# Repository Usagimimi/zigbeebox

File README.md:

# zigbeebox
Powerful zigbee coordinator with USB and debug port in metal enclosure.

### This project is still under development!!! 

## Description
[Zigbee in general.](https://en.wikipedia.org/wiki/Zigbee)

The coordinator is the central unit of the zigbee network, handling significant RF traffic in most cases. This project offers low-cost open-source hardware for this task, as a remix of many DIY coordinators out there. Takes a bit of time and basic soldering skills to assemble, but it can replace any manufacturers proprietary device when ready. Using the right firmware and server application, you can build a reliable, secure zigbee network without factory restrictions, involving almost any zigbee appliance. This opens the possibility to use IKEA Tradfri lights along with Xiaomi sensors, Philips Hue products, and many more in the same network, without the vendors gateway. The pcb utilizes a cheap chinese CC2538+CC2592 RF module with ARM Cortex-M3 based SoC and enough memory to serve a lot of connections with good performance.

The design heavily relies on open-source code, such as [Zigbee2MQTT](https://www.zigbee2mqtt.io) and various firmware.

## Features
* Zigbee 3.0 capable SoC with external antenna connector and RF amplifier frontend
* Use mostly THT and superior SMD components to allow soldering by hand with average tools
* PCB dimensions are designed to fit in a cheap metal enclosure for better shielding
* Avoid dongle-style layout to assist final placement away from any interference
* Mounted with convenient USB Type-C receptacle, detach & orientation sensing
* Plug & play firmware flashing on the J-Link compatible 20pin IDC header
* Indicator LEDs for power, allow join mode, ZNP activity (RF traffic)
* Self-regenerating polyfuse protection for USB host & device

*Since the pcb applies a considerable amount of copper under the CC2538+CC2592 module, it is highly recommended to use the IPEX connector and connect an external antenna, even without metal enclosure.*

## PCB BOM
The following components are needed to assemble the coordinator.

| Component  | Type | Package | Value | Quantity |
| ---------- | ---- | ------- | ----- | -------- |
| F1 | Polyfuse | SMD-1206 | Ih=250mA, It=500mA | 1 |
| R1-R2 | Resistor | SMD-1206 | 33Ω | 2 |
| R3 | Resistor | SMD-1206 | 1.5kΩ | 1 |
| R4-R6 | Resistor | SMD-1206 | 100Ω | 3 |
| R7 | Resistor | SMD-1206 | 1kΩ | 1 |
| R8-R9 | Resistor | SMD-1206 | 5.1kΩ | 2 |
| C1-C2 | Tantalum capacitor | SMD-1206 | 10uF | 2 |
| C3 | Capacitor | SMD-1206 | 100nF | 1 |
| C4-C5 | Capacitor | SMD-1206 | 47pF | 2 |
| PWR-JOIN-ACT | LED | 3mm THT | Vf=2.2V, If=10mA | 3 |
| LD1117 | Voltage regulator | SOT223 | LD1117S33TR | 1 |
| USB-C | Receptacle | 16-pin THT | GCT USB4085 | 1 |
| RESET | Tactile switch | 3-pin THT 4.5x4.5mm | TS-C017 | 1 |
| JLINK-JTAG | Connector | 2.54mm IDC double row | 20-pin keyed male | 1 |
| Pin header | Connector | 2.54mm single row | 4-pin male | 1 |

Additional parts:

| Component  | Type | Package | Quantity | Source |
| ---------- | ---- | ------- | -------- | ------ |
| *[CC2538+CC2592 Module](https://github.com/uzsito/CC2538-CC2592-kicad-component)* | *Zigbee RF board* | *33-pin 20.5x33mmm* | *1* | Aliexpress, Ebay |

## Flashing
You can download and burn compiled firmware from the following repositories:

| Repository  | Firmware | Tested |
| --------- | --------- | ------ |
| [reverieline/CC2538-CC2592-ZNP](https://github.com/reverieline/CC2538-CC2592-ZNP) | MODKAMRU_V3_USB.hex | Tested |
| [antst/CC2538-ZNP-Coordinator-firmware](https://github.com/antst/CC2538-ZNP-Coordinator-firmware) | | Not tested |
| [Koenkk/Z-Stack-firmware](https://github.com/Koenkk/Z-Stack-firmware) | | Not tested |

Flashing methods:
* Using [J-link and J-Flash application](https://github.com/uzsito/zigbeebox/wiki/Flashing-with-JLink), connecting to 20-pin header with ribbon cable (Tested)
* Using [Raspberry Pi and OpenOCD](https://gist.github.com/hwhw/fc43892785aa84913d03495c97b0f25a) connecting with dupont wires (Not tested)

## Enclosure
It is optional to [put the board in a cheap metal case](https://github.com/uzsito/zigbeebox/wiki/Installing-in-metal-box) to achieve better shielding and appearance. The finished pcb fits perfectly in a common box by design, with an applied pigtail to connect your external antenna.

*Finished photos and cutout templates coming soon.*

Former prototype:

## Assembly and application
1. Clone or download this repository.
2. Use the prebuilt [gerber archive](kicad_board/gerber/zigbeebox.zip) to print the pcb. Any chinese manufacturer (JLPCB, ALLPCB, PCBWAY, etc.) can fabricate a copy for a couple dollars. Really, it's dirt cheap.
3. Once you got the pcb and the listed components, assemble the coordinator by hand soldering, no special tool needed.
4. Flash the desired firmware with one of the available methods.
5. Connect the board to a machine running zigbee2mqtt or other zigbee server application, and check the log for your new coordinator.

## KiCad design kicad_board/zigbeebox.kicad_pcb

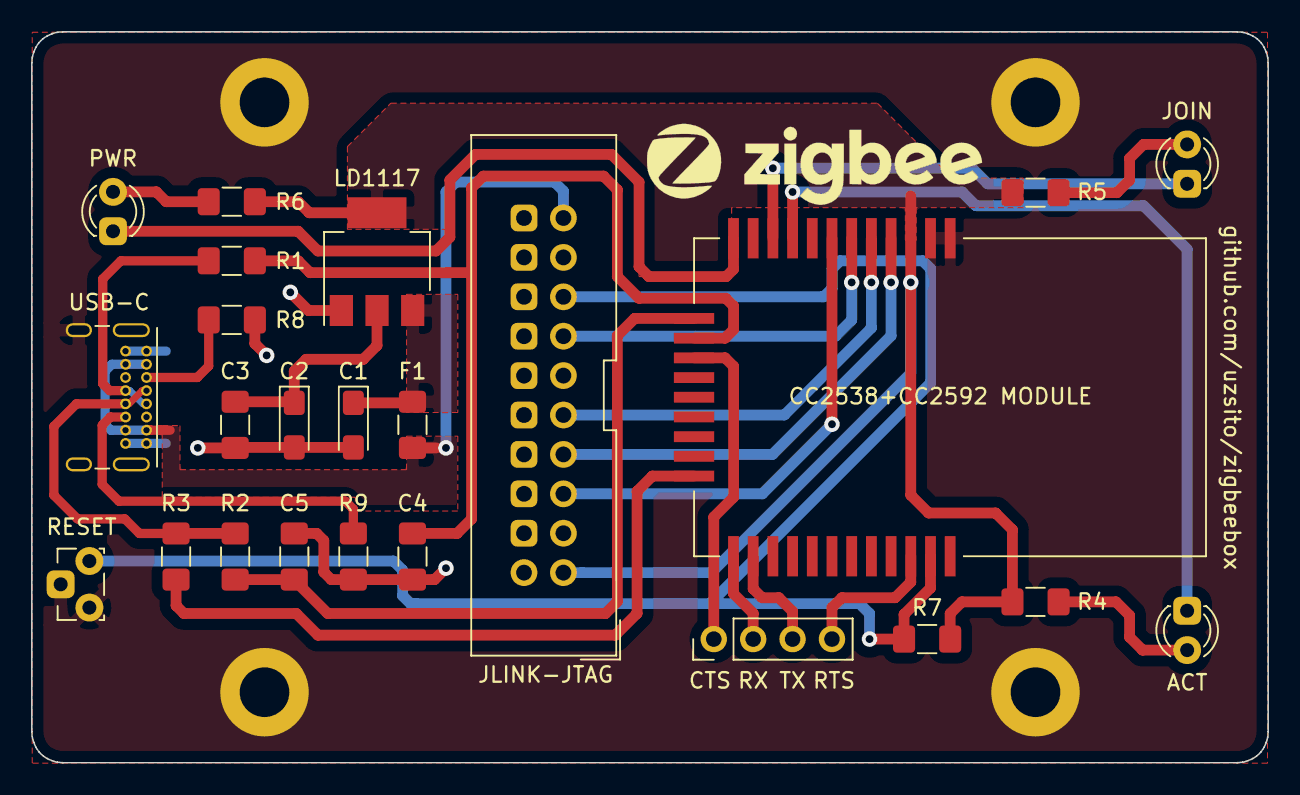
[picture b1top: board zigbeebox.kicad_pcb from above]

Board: 2 copper layers, 79.7 x 47.1 mm, 28 parts (0 on the bottom side), 26 nets.

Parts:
C1, C2: 10uF; CP_EIA-3216-12_Kemet-S_Pad1.58x1.35mm_HandSolder
C3: 100nF; C_1206_3216Metric_Pad1.42x1.75mm_HandSolder
C4, C5: 47pF; C_1206_3216Metric_Pad1.42x1.75mm_HandSolder
F1: Fuse; Fuse_1206_3216Metric_Pad1.42x1.75mm_HandSolder
H1, H2, H3, H4: MountingHole_Pad; MountingHole_3.2mm_M3_ISO7380_Pad
J1: Debug; PinHeader_1x04_P2.54mm_Vertical
J2: JLINK-JTAG; IDC-Header_2x10_P2.54mm_Vertical
LD1117: LD1117S33TR_SOT223; SOT-223-3_TabPin2
LED1: ACT; LED_D3.0mm
LED2: JOIN; LED_D3.0mm
LED3: PWR; LED_D3.0mm
R1, R2: 33R; R_1206_3216Metric_Pad1.42x1.75mm_HandSolder
R3: 1.5K; R_1206_3216Metric_Pad1.42x1.75mm_HandSolder
R4, R5, R6: 100R; R_1206_3216Metric_Pad1.42x1.75mm_HandSolder
R7: 1k; R_1206_3216Metric_Pad1.42x1.75mm_HandSolder
R8, R9: 5.1k; R_1206_3216Metric_Pad1.42x1.75mm_HandSolder
SW1: RESET; SW_Tactile_PUSH_Angled_4.5mm_H6.0mm_TS_C017
U1: CC2538+CC2592 MODULE; CC2538_CC2592
USB1: USB-C; USB_C_Receptacle_GCT_USB4085

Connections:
GND: C1.2, C2.2, C3.2, C4.2, C5.2, H1.1, H2.1, H3.1, H4.1, J2.4, J2.6, J2.8, J2.10, J2.12, J2.14, J2.16, J2.18, J2.20, LD1117.1, R8.2, R9.2, SW1.1, SW1.3, U1.1, U1.2, USB1.A1, USB1.A12, USB1.B1, USB1.B12, USB1.S1
unnamed: C1.1, F1.1, LD1117.3
unnamed: C2.1, C3.1, J2.1, LD1117.2, R4.1, R5.1, R6.1, R7.1, U1.3
unnamed: C4.1, R1.2, U1.14
unnamed: C5.1, R2.2, U1.13
unnamed: F1.2, J2.19, USB1.A4, USB1.A9, USB1.B4, USB1.B9
unnamed: J1.1, U1.15
unnamed: J1.2, U1.22
unnamed: J1.3, U1.23
unnamed: J1.4, U1.31
unnamed: J2.5, U1.7
unnamed: J2.7, U1.4
unnamed: J2.9, U1.5
unnamed: J2.13, U1.6
unnamed: J2.15, R7.2, SW1.2, U1.32
unnamed: LED1.1, U1.9
unnamed: LED1.2, R4.2
unnamed: LED2.1, U1.10
unnamed: LED2.2, R5.2
unnamed: LED3.1, U1.12
unnamed: LED3.2, R6.2
unnamed: R1.1, USB1.A7, USB1.B7
unnamed: R2.1, R3.1, USB1.A6, USB1.B6
unnamed: R3.2, U1.21
unnamed: R8.1, USB1.A5
unnamed: R9.1, USB1.B5

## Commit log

2020-03-30 Added graphics
2020-06-02 Enclosure pictures
2020-06-21 Kicad board CC2538
2020-06-21 Previous version graphics
2020-06-21 Update renders
2020-06-21 Gerber files
2020-06-21 Upload enclosure pictures
2020-06-22 Minor trace width adjustments
2020-06-22 Gerber update
2020-06-22 Render update
2020-06-22 Update graphics
2020-06-22 J-Link pictures
